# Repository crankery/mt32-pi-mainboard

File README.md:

# mt32-pi-mainboard

A host board for the [mt32-pi project](https://github.com/dwhinham/mt32-pi). I've tried to use nothing but cheap through-hole parts off Aliexpress for this to make it easy to build. I had one of the LCD2004 modules in a drawer which is why I used that huge thing. The board is 100x100mm which should be pretty cheap to get fabricated.

> [!NOTE]
> This is untested and probably doesn't work. If it ends up working, I'll make a 3D printable case for it.

Yeah, the DAC module model I found has some weird transparancy issues in Kicad.

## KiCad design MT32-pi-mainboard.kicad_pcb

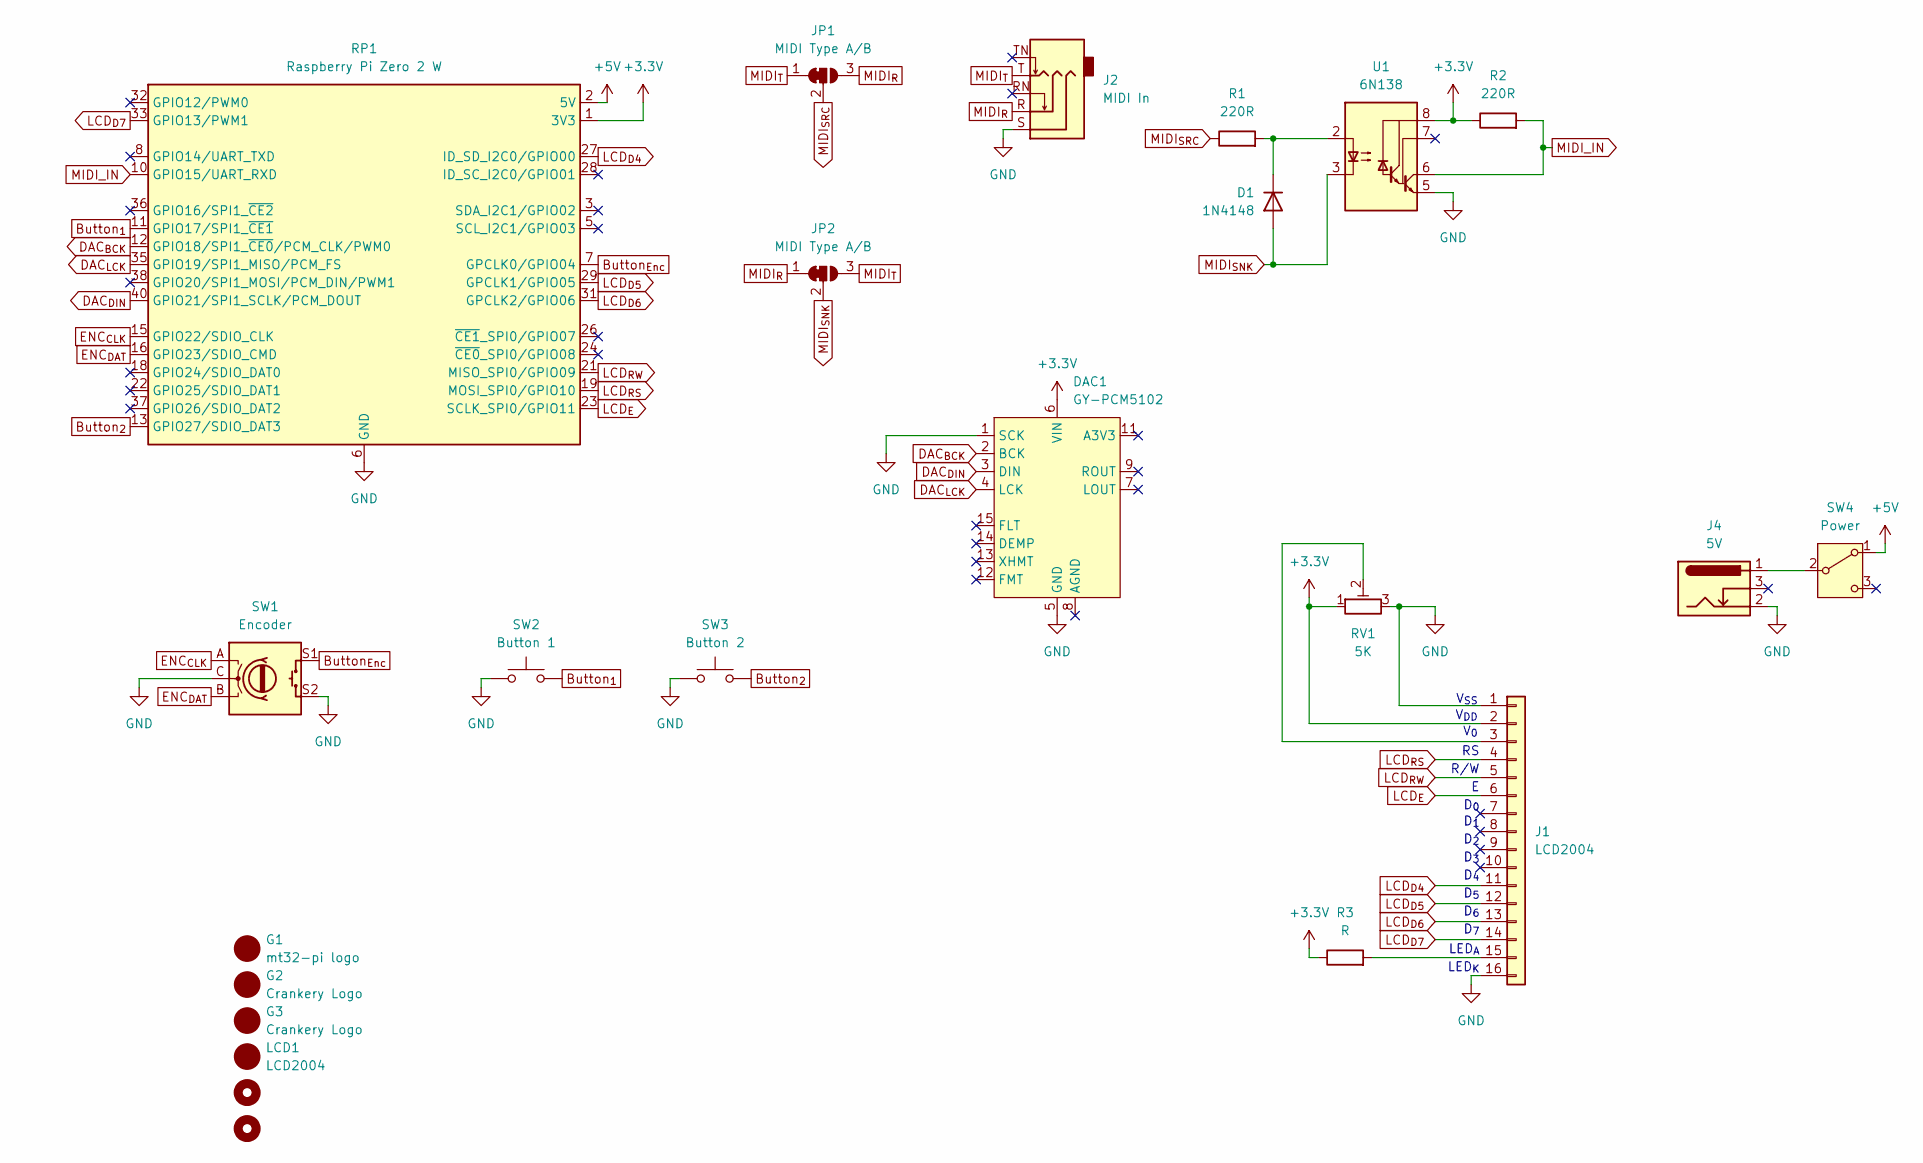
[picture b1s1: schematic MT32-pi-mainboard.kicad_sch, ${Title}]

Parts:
D1: 1N4148; D_DO-35_SOD27_P7.62mm_Horizontal
DAC1: GY-PCM5102
G1: mt32-pi logo; mt32-pi-logo
G2, G3: Crankery Logo; crankery_small
H2, H3: MountingHole; MountingHole_2.7mm_M2.5
J1: LCD2004; PinSocket_1x16_P2.54mm_Horizontal
J2: MIDI In; PJ-307
J4: 5V; BarrelJack_Horizontal
JP1, JP2: MIDI Type A/B; SolderJumper-3_P1.3mm_Bridged12_RoundedPad1.0x1.5mm
LCD1: LCD2004
R1, R2: 220R; R_Axial_DIN0207_L6.3mm_D2.5mm_P7.62mm_Horizontal
R3: R; R_Axial_DIN0207_L6.3mm_D2.5mm_P7.62mm_Horizontal
RP1: Raspberry Pi Zero 2 W; RP_Zero_2W
RV1: 5K; Potentiometer_Runtron_RM-065_Vertical
SW1: Encoder; RotaryEncoder_Alps_EC11E-Switch_Vertical_H20mm
SW2: Button 1; SW_Cherry_MX_1.00u_PCB
SW3: Button 2; SW_Cherry_MX_1.00u_PCB
SW4: Power; SK12D07VG4
U1: 6N138; DIP-8_W7.62mm

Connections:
+3.3V: DAC1.6 (VIN), J1.2, R2.1, R3.1, RP1.1 (3V3), RP1.17 (3V3), RV1.1, U1.8 (VCC)
+5V: RP1.2 (5V), RP1.4 (5V), SW4.1 (A)
Button_{1}: RP1.11 (GPIO17/SPI1_~CE1), SW2.2
Button_{2}: RP1.13 (GPIO27/SDIO_DAT3), SW3.2
Button_{Enc}: RP1.7 (GPCLK0/GPIO04), SW1.S1
DAC_{BCK}: DAC1.2 (BCK), RP1.12 (GPIO18/SPI1_~CE0/PCM_CLK/PWM0)
DAC_{DIN}: DAC1.3 (DIN), RP1.40 (GPIO21/SPI1_SCLK/PCM_DOUT)
DAC_{LCK}: DAC1.4 (LCK), RP1.35 (GPIO19/SPI1_MISO/PCM_FS)
ENC_{CLK}: RP1.15 (GPIO22/SDIO_CLK), SW1.A
ENC_{DAT}: RP1.16 (GPIO23/SDIO_CMD), SW1.B
GND: DAC1.1 (SCK), DAC1.5 (GND), J1.1, J1.16, J2.S, J4.2, RP1.6 (GND), RP1.9 (GND), RP1.14 (GND), RP1.20 (GND), RP1.25 (GND), RP1.30 (GND), RP1.34 (GND), RP1.39 (GND), RV1.3, SW1.C, SW1.S2, SW2.1, SW3.1, U1.5 (GND)
LCD_{D4}: J1.11, RP1.27 (ID_SD_I2C0/GPIO00)
LCD_{D5}: J1.12, RP1.29 (GPCLK1/GPIO05)
LCD_{D6}: J1.13, RP1.31 (GPCLK2/GPIO06)
LCD_{D7}: J1.14, RP1.33 (GPIO13/PWM1)
LCD_{E}: J1.6, RP1.23 (SCLK_SPI0/GPIO11)
LCD_{RS}: J1.4, RP1.19 (MOSI_SPI0/GPIO10)
LCD_{RW}: J1.5, RP1.21 (MISO_SPI0/GPIO09)
MIDI_IN: R2.2, RP1.10 (GPIO15/UART_RXD), U1.6 (VO2)
MIDI_{R}: J2.R, JP1.3 (B), JP2.1 (A)
MIDI_{SNK}: D1.2 (A), JP2.2 (C), U1.3 (C2)
MIDI_{SRC}: JP1.2 (C), R1.1
MIDI_{T}: J2.T, JP1.1 (A), JP2.3 (B)
unnamed: D1.1 (K), R1.2, U1.2 (C1)
unnamed: J1.3, RV1.2
unnamed: J1.15, R3.2
unnamed: J4.1, SW4.2 (B)

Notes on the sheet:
D_{7}
LED_{A}
D_{6}
D_{1}
R/W
LED_{K}
V_{SS}
V_{0}
D_{3}
D_{2}
D_{4}
D_{5}
D_{0}
V_{DD}

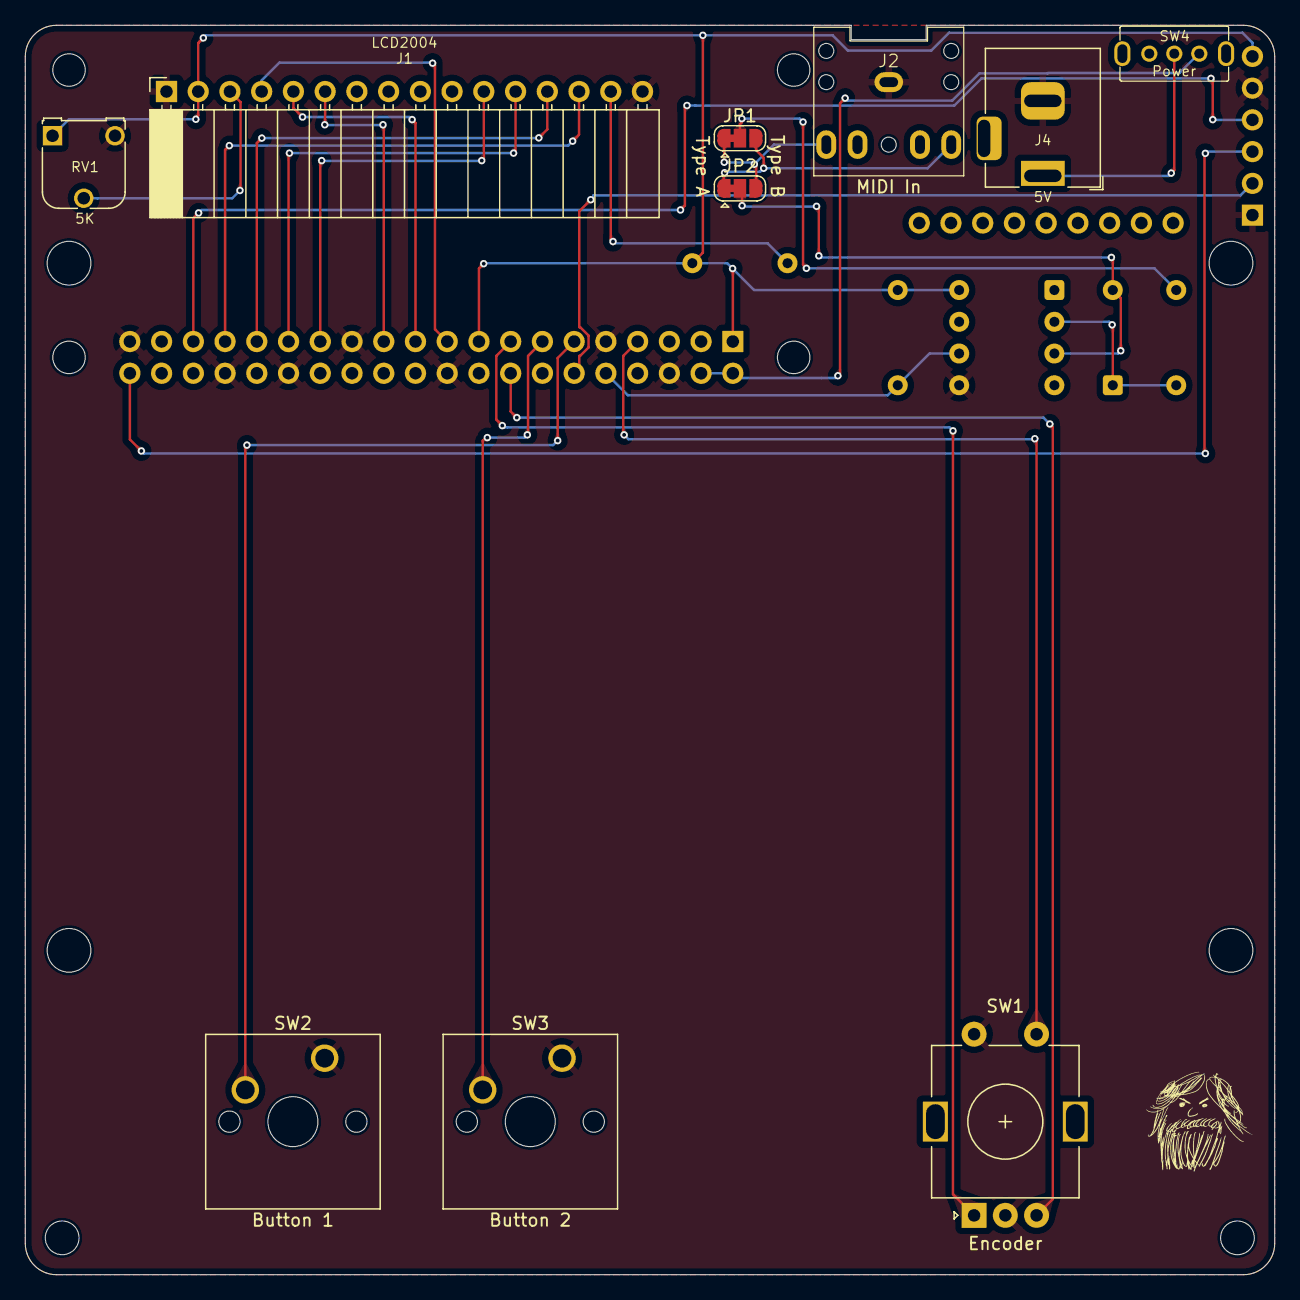
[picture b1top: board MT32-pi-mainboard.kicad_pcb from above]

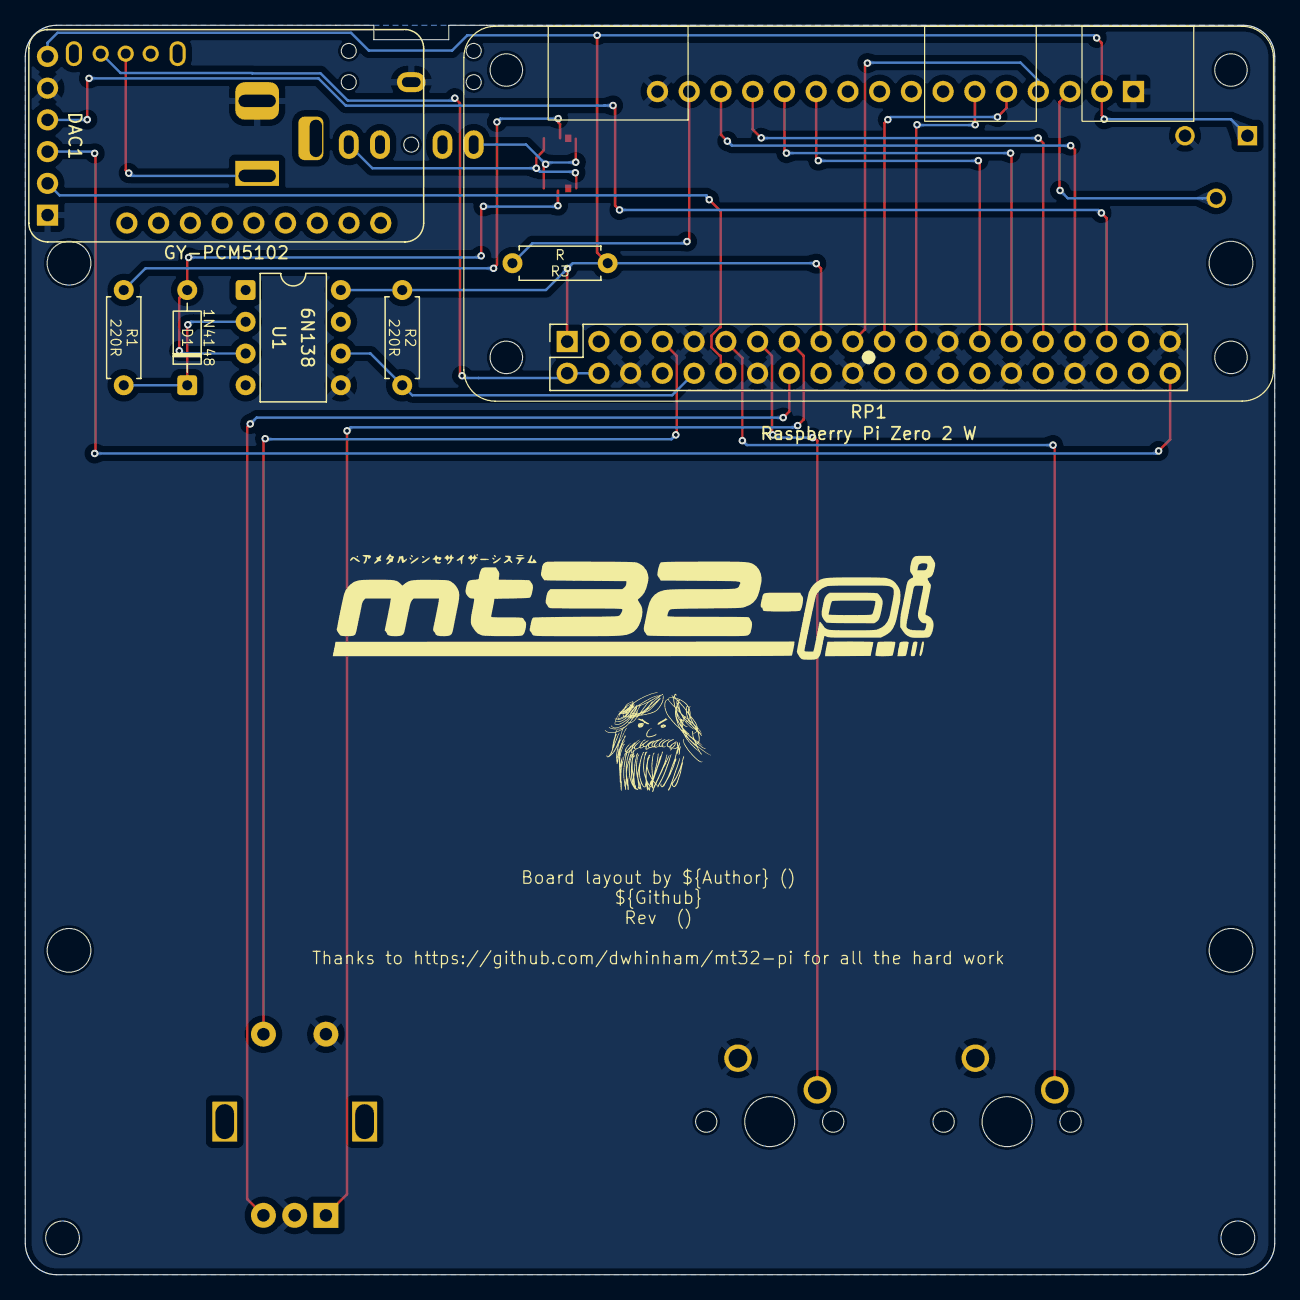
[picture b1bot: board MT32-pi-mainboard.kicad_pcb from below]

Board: 2 copper layers, 100.0 x 100.0 mm, 23 parts (7 on the bottom side), 27 nets.

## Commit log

2026-02-17 Enhance README with project details and warnings
    Expanded project description and added a note about untested status.
2026-02-17 Update README with project details and notes
    Expanded description of the mt32-pi project and added note about potential 3D printable case.
2026-02-17 Improve README description for mt32-pi project
    grammar
2026-02-17 add symbols for virtual models and graphics
2026-02-17 cleanup, add gerbers
2026-02-17 clean up silks, use project properties for text
2026-02-17 regenerate gerbers
2026-02-17 add some renders and the zipped gerbers
2026-02-17 Add images to README for MT32-pi mainboard
    Added images of the MT32-pi mainboard to the README.
2026-02-17 remove duplicate file
